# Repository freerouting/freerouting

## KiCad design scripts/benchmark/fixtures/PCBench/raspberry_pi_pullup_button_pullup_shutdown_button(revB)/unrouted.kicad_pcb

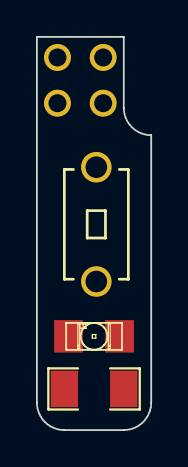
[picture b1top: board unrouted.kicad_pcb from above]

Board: 2 copper layers, 6.4 x 21.8 mm, 4 parts (0 on the bottom side), 4 nets, no tracks yet.

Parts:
D1: LED; LED-1206
R1: R; SM1206
SW1: SW_PUSH; button_single_custom
U1: PI_SHUTDOWN; pi_shutdown_4pin

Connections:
unnamed: D1.1, U1.16
unnamed: R1.1, SW1.1, U1.14
unnamed: SW1.2, U1.15
unnamed: D1.2, R1.2

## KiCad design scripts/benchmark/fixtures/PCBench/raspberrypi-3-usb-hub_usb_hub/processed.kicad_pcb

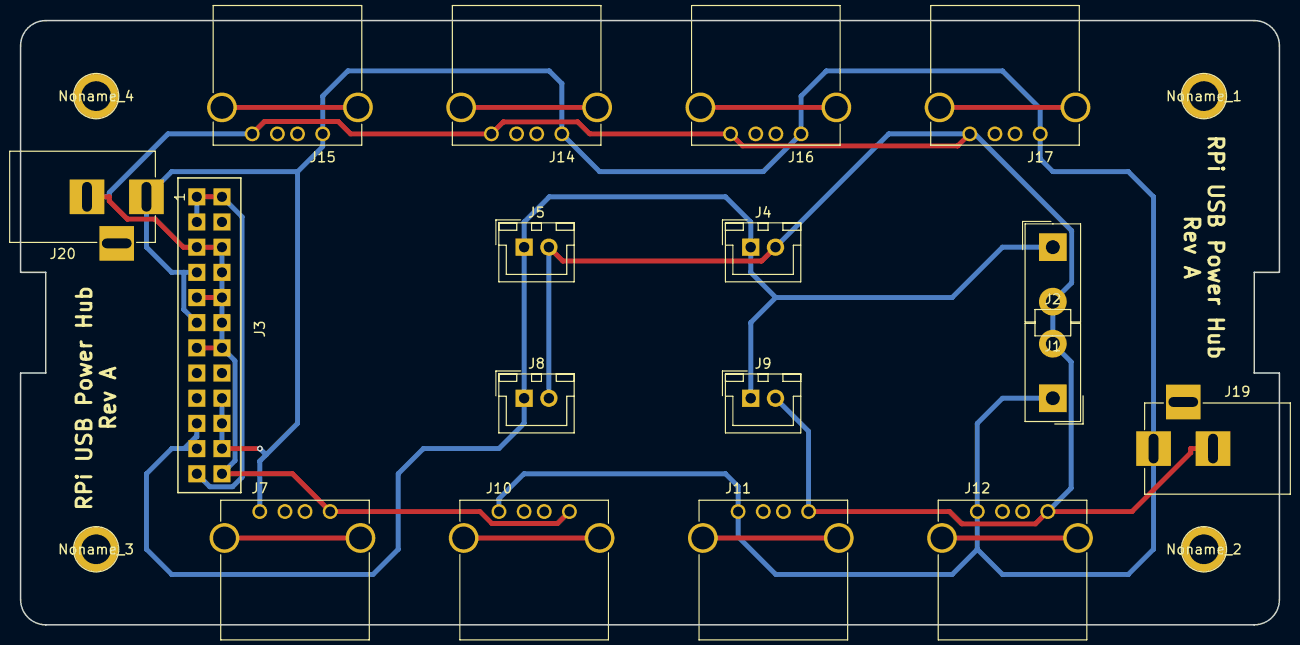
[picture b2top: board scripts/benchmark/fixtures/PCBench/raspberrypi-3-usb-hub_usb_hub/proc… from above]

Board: 2 copper layers, 127.0 x 61.0 mm, 21 parts (0 on the bottom side), 4 nets.

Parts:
J1, J2: CONN_01X02_MALE-B2B; Molex_MiniFit-JR-5556-02A_2x01x4.20mm_Straight
J3: DIL24; ATX_Wire_On_Board
J4, J5, J8, J9: CONN_01X02_MALE; JST_XH_B02B-XH-A_02x2.50mm_Straight
J7, J10, J11, J12, J14, J15, J16, J17: USB_A
J19, J20: CONN_COAXIAL; BARREL_JACK
Noname_1, Noname_2, Noname_3, Noname_4: 1pin

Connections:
+3V3: J3.1, J3.2, J3.12, J3.13
+5V: J2.1, J3.4, J3.6, J3.21, J3.22, J3.23, J7.1, J10.1, J11.1, J12.1, J14.1, J15.1, J16.1, J17.1, J19.1, J20.1
+12V: J1.1, J3.10, J3.11, J4.1, J5.1, J8.1, J9.1
GND: J1.2, J2.2, J3.3, J3.5, J3.7, J3.15, J3.16, J3.17, J3.18, J3.19, J3.24, J4.2, J5.2, J7.4, J8.2, J9.2, J10.4, J11.4, J12.4, J14.4, J15.4, J16.4, J17.4, J19.2, J20.2

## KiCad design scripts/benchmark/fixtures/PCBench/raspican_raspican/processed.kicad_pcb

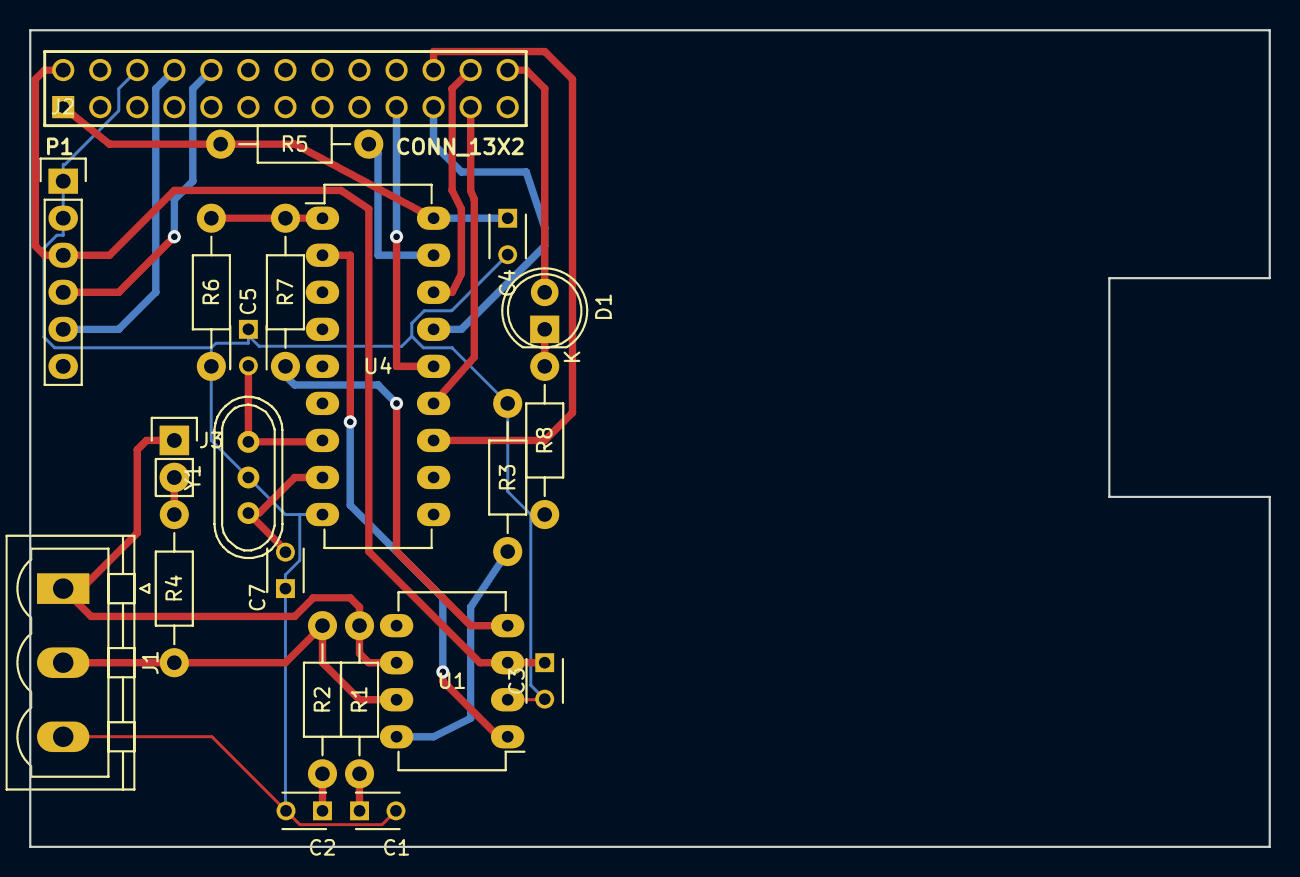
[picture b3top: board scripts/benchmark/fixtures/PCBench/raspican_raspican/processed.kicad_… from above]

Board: 2 copper layers, 85.0 x 56.0 mm, 22 parts (0 on the bottom side), 24 nets.

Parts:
C1, C2: 560pF; C_Disc_D3_P2.5
C3, C4: 0.1μF; C_Disc_D3_P2.5
C5, C7: 22pF; C_Disc_D3_P2.5
D1: LED; LED-5MM
J1: CANBUS; PhoenixContact_MSTBVA-G_03x5.08mm_Vertical
J2: TTL_SERIAL; Pin_Header_Straight_1x06
J3: TERMINATE; Pin_Header_Straight_1x02
P1: CONN_13X2; pin_array_13x2
R1, R2: 100Ω; Resistor_Horizontal_RM10mm
R3, R5: 4K7Ω; Resistor_Horizontal_RM10mm
R4: 120Ω; Resistor_Horizontal_RM10mm
R6: 18KΩ; Resistor_Horizontal_RM10mm
R7: 10KΩ; Resistor_Horizontal_RM10mm
R8: 1KΩ; Resistor_Horizontal_RM10mm
U1: MCP2551-I/P; DIP-8_W7.62mm_LongPads
U4: MCP2515; DIP-18_W7.62mm_LongPads
Y1: 16MHz; Crystal_HC49-U_Vertical_3Pin

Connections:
+3.3V: C4.1, P1.1, R5.1, U4.18
+5V: C3.1, J2.3, P1.2, U1.3
/CANH: J1.2, R2.1, R4.1, U1.7
/CANL: J1.1, J3.1, R1.1, U1.6
/GPIO7(CE1): D1.2, P1.26
/GPIO8(CE0): P1.24, U4.16
/GPIO9(MISO): P1.21, U4.15
/GPIO10(MOSI): P1.19, U4.14
/GPIO11(SCLK): P1.23, U4.13
/GPIO25: P1.22, U4.12
/RXD: J2.4, P1.10
/TXD: J2.5, P1.8
GND: C1.2, C2.2, C3.2, C4.2, C5.1, C7.1, J1.3, J2.1, J2.2, P1.6, R3.1, R6.2, R8.1, U1.2, U4.9, Y1.3
unnamed: C1.1, R1.2
unnamed: C2.1, R2.2
unnamed: C5.2, U4.7, Y1.2
unnamed: C7.2, U4.8, Y1.1
unnamed: D1.1, R8.2
unnamed: J3.2, R4.2
unnamed: R3.2, U1.8
unnamed: R5.2, U4.17
unnamed: R6.1, R7.2, U4.1
unnamed: R7.1, U1.4
unnamed: U1.1, U4.2
